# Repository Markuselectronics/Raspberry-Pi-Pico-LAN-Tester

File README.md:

<div align="center">

# Raspberry Pi Pico LAN Tester

### Portable Ethernet diagnostic tool with `W5500`, `OLED`, battery charging and a custom PCB

</div>

---

## Overview

This is a compact handheld LAN tester based on a **Raspberry Pi Pico**, a **W5500 Ethernet controller**, an **SSD1306 OLED display** and **LiPo battery charging**.

It quickly checks whether an Ethernet port is actually working. The tester checks the physical link, requests an IP address with DHCP, shows IP / gateway / DNS information and performs a simple internet connectivity test.

---

## Main Features

- `W5500` Ethernet controller over SPI
- `SSD1306` 128x64 OLED display
- One-button LAN test
- Link, DHCP and internet check
- IP / Gateway / DNS display
- Battery voltage and charging status
- Custom PCB with Raspberry Pi Pico
- 3D printed enclosure

---

## Project Files

The repository contains the firmware and KiCad hardware files:

```text
LANTester/
├── Code/
└── KiCad/
```

`Code` contains the Raspberry Pi Pico firmware.  
`KiCad` contains the schematic, PCB and manufacturing files.

---

## Flashing

If the ready-built `LANTester.uf2` file is included, flashing is simple:

1. Hold **BOOTSEL** on the Raspberry Pi Pico.
2. Plug it into USB.
3. Copy `LANTester.uf2` to the Pico drive.
4. The Pico reboots and starts the firmware.

No special programmer is needed.

---

## Full Build Guide

Instructables:  
https://www.instructables.com/Portable-Raspberry-Pi-Pico-LAN-Tester/

---

## 3D Printed Case

Printables:  
https://www.printables.com/model/1705220-raspberry-pi-pico-lan-tester

---

## Notes

This repository contains the firmware and hardware files for the project.  
Photos, build steps and assembly instructions are documented in the Instructables guide.

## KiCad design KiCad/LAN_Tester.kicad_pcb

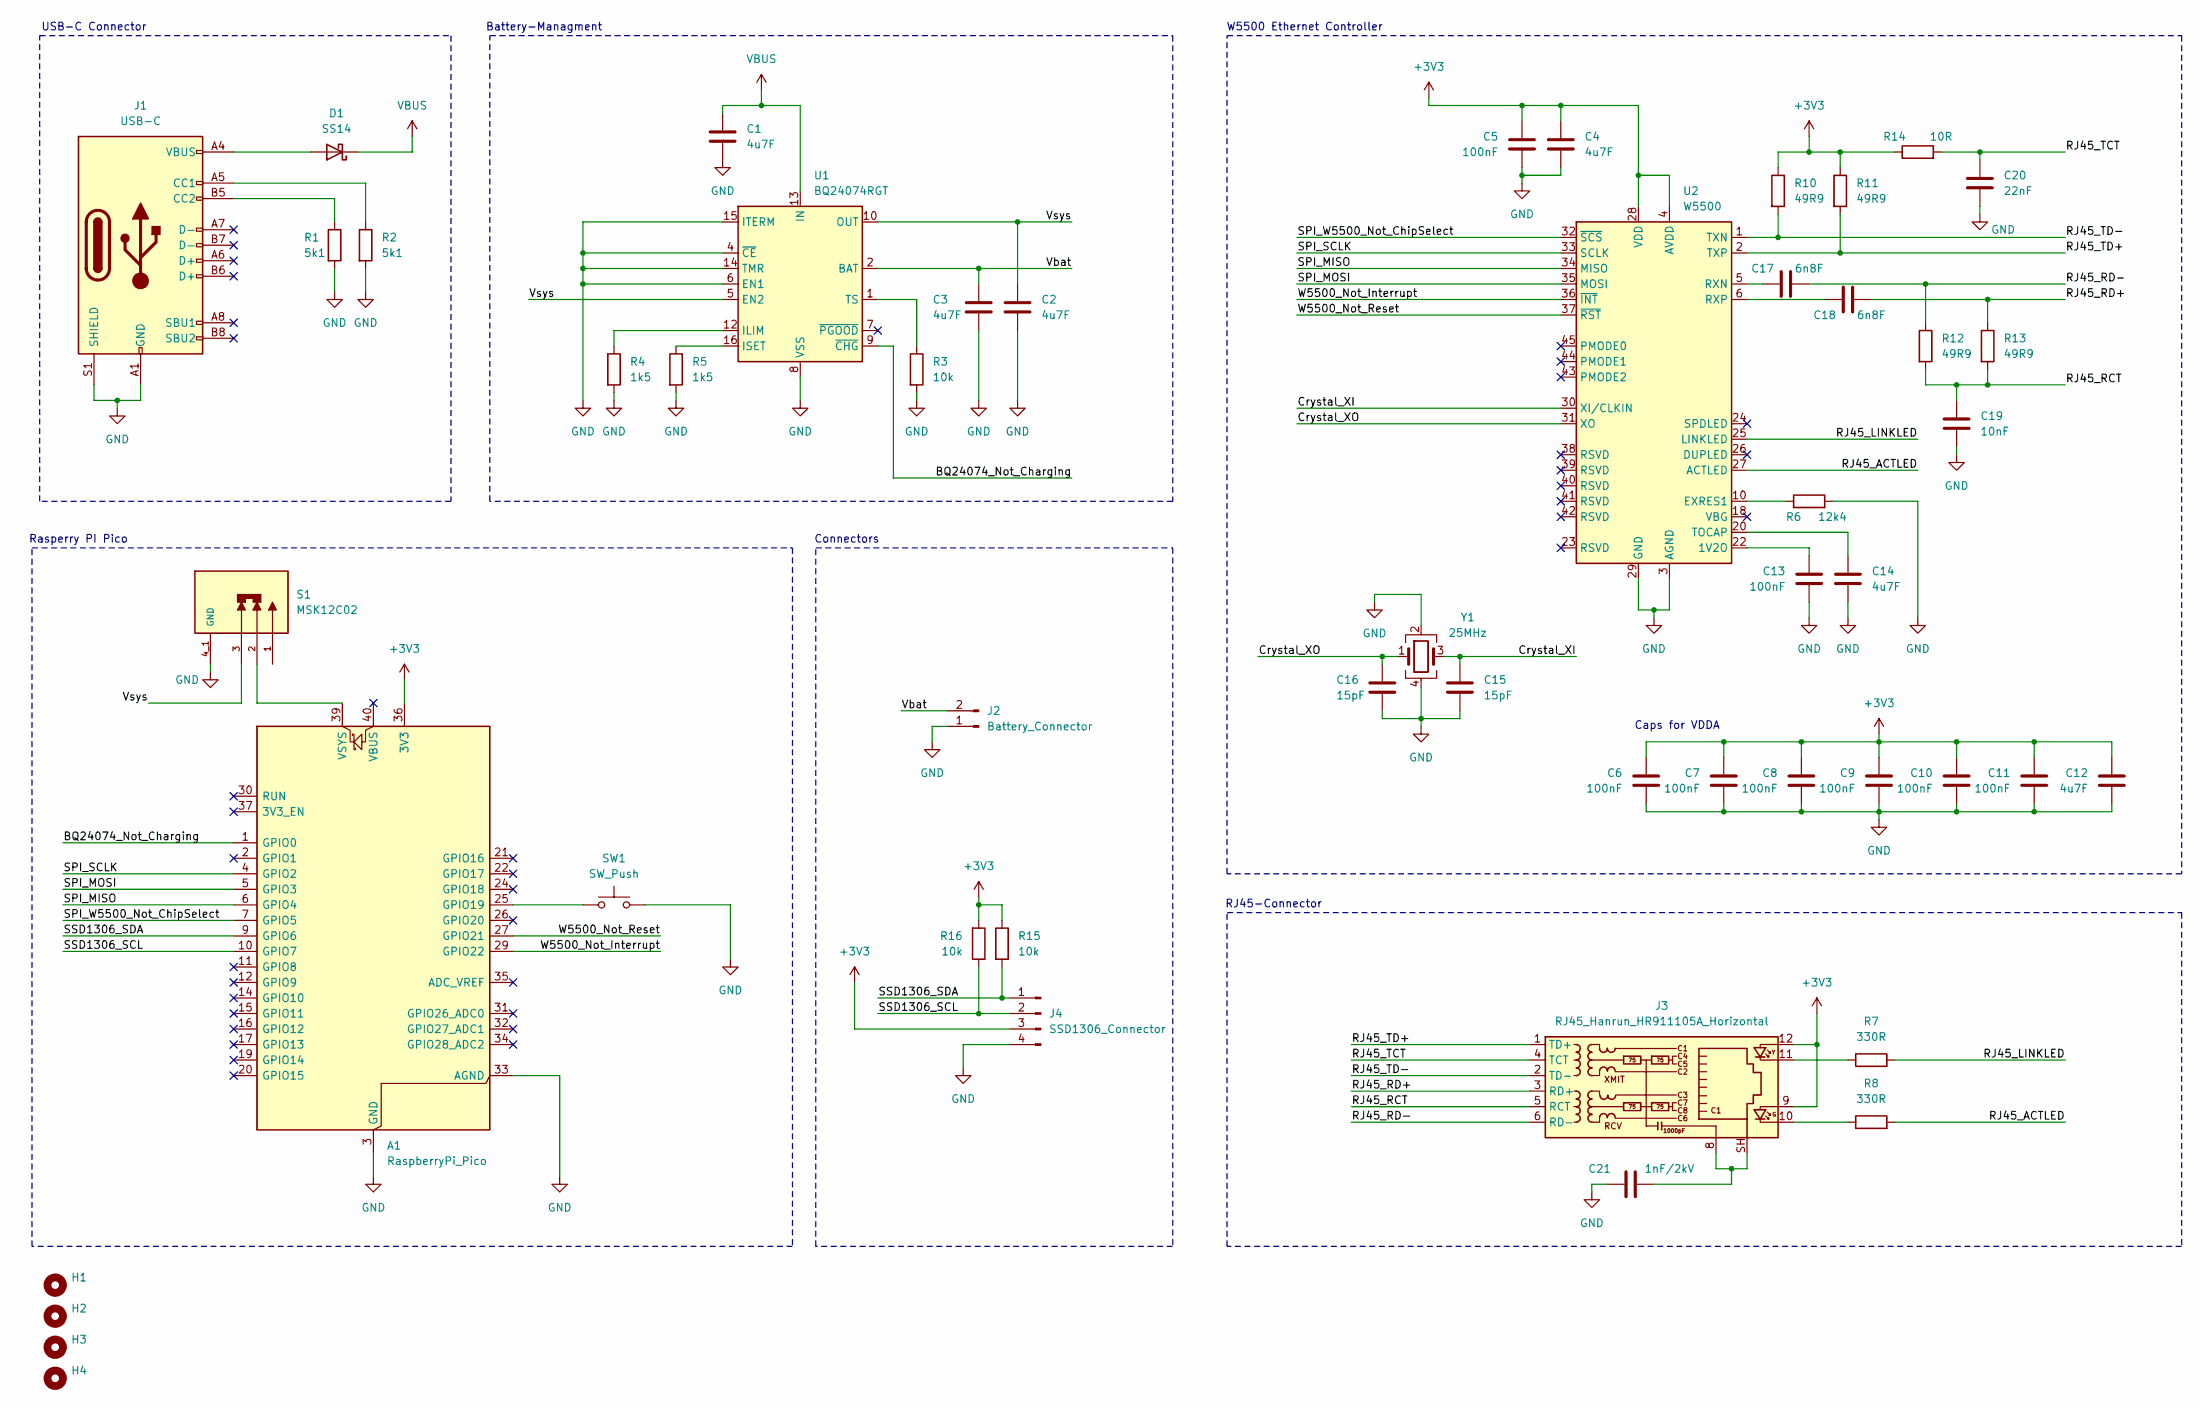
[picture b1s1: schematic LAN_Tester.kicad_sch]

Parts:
A1: RaspberryPi_Pico; RaspberryPi_Pico_SMD
C1, C2, C3, C4, C12, C14: 4u7F; C_0805_2012Metric; LCSC Part # C1779
C5, C6, C7, C8, C9, C10, C11, C13: 100nF; C_0402_1005Metric; LCSC Part # C307331
C15, C16: 15pF; C_0603_1608Metric; LCSC Part # C1644
C17, C18: 6n8F; C_0603_1608Metric; LCSC Part # C1631
C19: 10nF; C_0603_1608Metric; LCSC Part # C57112
C20: 22nF; C_0603_1608Metric; LCSC Part # C1697
C21: 1nF/2kV; C_1206_3216Metric; LCSC Part # C9196
D1: SS14; D_SMA; LCSC Part # C2480
H1, H2, H3, H4: MountingHole; MountingHole_3.5mm
J1: USB-C; SHOU HAN TYPE-C 16PIN 2MD(073); LCSC Part # C2765186
J2: Battery_Connector; JST_PH_S2B-PH-SM4-TB_1x02-1MP_P2.00mm_Horizontal; LCSC Part # C295747
J3: RJ45_Hanrun_HR911105A_Horizontal; LCSC Part # C12074
J4: SSD1306_Connector; PinHeader_1x04_P2.54mm_Vertical
R1, R2: 5k1; C_0603_1608Metric; LCSC Part # C23186
R3, R15, R16: 10k; C_0603_1608Metric; LCSC Part # C25804
R4, R5: 1k5; C_0603_1608Metric; LCSC Part # C22843
R6: 12k4; C_0603_1608Metric; LCSC Part # C22865
R7, R8: 330R; C_0603_1608Metric; LCSC Part # C23138
R10, R11, R12, R13: 49R9; C_0603_1608Metric; LCSC Part # C23184
R14: 10R; C_0603_1608Metric; LCSC Part # C22859
S1: MSK12C02; SW_MSK12C02; PARTREV A/0; LCSC Part # C431540
SW1: SW_Push; SW_PUSH_6mm_H4.3mm; LCSC Part # C29781307
U1: BQ24074RGT; VQFN-16-1EP_3x3mm_P0.5mm_EP1.6x1.6mm; LCSC Part # C2861252
U2: W5500; LQFP-48_7x7mm_P0.5mm; LCSC Part # C32843
Y1: 25MHz; Crystal_SMD_3225-4Pin_3.2x2.5mm; LCSC Part # C9006

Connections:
+3V3: A1.36 (3V3), C4.1, C5.1, C6.1, C7.1, C8.1, C9.1, C10.1, C11.1, C12.1, J3.9, J3.12, J4.3, R10.1, R11.1, R14.1, R15.1, R16.2, U2.4 (AVDD), U2.8 (AVDD), U2.11 (AVDD), U2.15 (AVDD), U2.17 (AVDD), U2.21 (AVDD), U2.28 (VDD)
/BQ24074_Not_Charging: A1.1 (GPIO0), U1.9 (~CHG)
/Crystal_XI: C15.1, U2.30 (XI/CLKIN), Y1.3
/Crystal_XO: C16.1, U2.31 (XO), Y1.1
/RJ45_ACTLED: R8.2, U2.27 (ACTLED)
/RJ45_LINKLED: R7.2, U2.25 (LINKLED)
/RJ45_RCT: C19.1, J3.5 (RCT), R12.2, R13.2
/RJ45_RD+: C18.2, J3.3 (RD+), R13.1
/RJ45_RD-: C17.2, J3.6 (RD-), R12.1
/RJ45_TCT: C20.1, J3.4 (TCT), R14.2
/RJ45_TD+: J3.1 (TD+), R11.2, U2.2 (TXP)
/RJ45_TD-: J3.2 (TD-), R10.2, U2.1 (TXN)
/SPI_MISO: A1.6 (GPIO4), U2.34 (MISO)
/SPI_MOSI: A1.5 (GPIO3), U2.35 (MOSI)
/SPI_SCLK: A1.4 (GPIO2), U2.33 (SCLK)
/SPI_W5500_Not_ChipSelect: A1.7 (GPIO5), U2.32 (~SCS)
/SSD1306_SCL: A1.10 (GPIO7), J4.2, R16.1
/SSD1306_SDA: A1.9 (GPIO6), J4.1, R15.2
/Vbat: C3.1, J2.2, U1.2 (BAT), U1.3 (BAT)
/Vsys: C2.1, S1.3, U1.5 (EN2), U1.10 (OUT), U1.11 (OUT)
/W5500_Not_Interrupt: A1.29 (GPIO22), U2.36 (~INT)
/W5500_Not_Reset: A1.27 (GPIO21), U2.37 (~RST)
GND: A1.3 (GND), A1.8 (GND), A1.13 (GND), A1.18 (GND), A1.23 (GND), A1.28 (GND), A1.33 (AGND), A1.38 (GND), C1.2, C2.2, C3.2, C4.2, C5.2, C6.2, C7.2, C8.2, C9.2, C10.2, C11.2, C12.2, C13.2, C14.2, C15.2, C16.2, C19.2, C20.2, C21.1, J1.A1 (GND), J1.A12 (GND), J1.B1 (GND), J1.B12 (GND), J1.S1 (SHIELD), J2.1, J4.4, R1.2, R2.2, R3.2, R4.2, R5.2, R6.2, S1.4_1 (GND), S1.4_2 (GND), S1.4_3 (GND), S1.4_4 (GND), SW1.2, U1.4 (~CE), U1.6 (EN1), U1.8 (VSS), U1.14 (TMR), U1.15 (ITERM), U1.17 (VSS), U2.3 (AGND), U2.9 (AGND), U2.14 (AGND), U2.16 (AGND), U2.19 (AGND), U2.29 (GND), U2.48 (AGND), Y1.2, Y1.4
unnamed: A1.25 (GPIO19), SW1.1
unnamed: A1.39 (VSYS), S1.2
unnamed: C21.2, J3.8, J3.SH
unnamed: D1.2 (A), J1.A4 (VBUS), J1.A9 (VBUS), J1.B4 (VBUS), J1.B9 (VBUS)
unnamed: J1.A5 (CC1), R2.1
unnamed: J1.B5 (CC2), R1.1
unnamed: J3.10, R8.1
unnamed: J3.11, R7.1
unnamed: R4.1, U1.12 (ILIM)
unnamed: R5.1, U1.16 (ISET)
unnamed: R3.1, U1.1 (TS)
unnamed: C13.1, U2.22 (1V2O)
unnamed: R6.1, U2.10 (EXRES1)
unnamed: C17.1, U2.5 (RXN)
unnamed: C18.1, U2.6 (RXP)
unnamed: C14.1, U2.20 (TOCAP)
VBUS: C1.1, D1.1 (K), U1.13 (IN)

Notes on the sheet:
Rasperry PI Pico
Caps for VDDA
RJ45-Connector
Connectors
Battery-Managment
W5500 Ethernet Controller
USB-C Connector

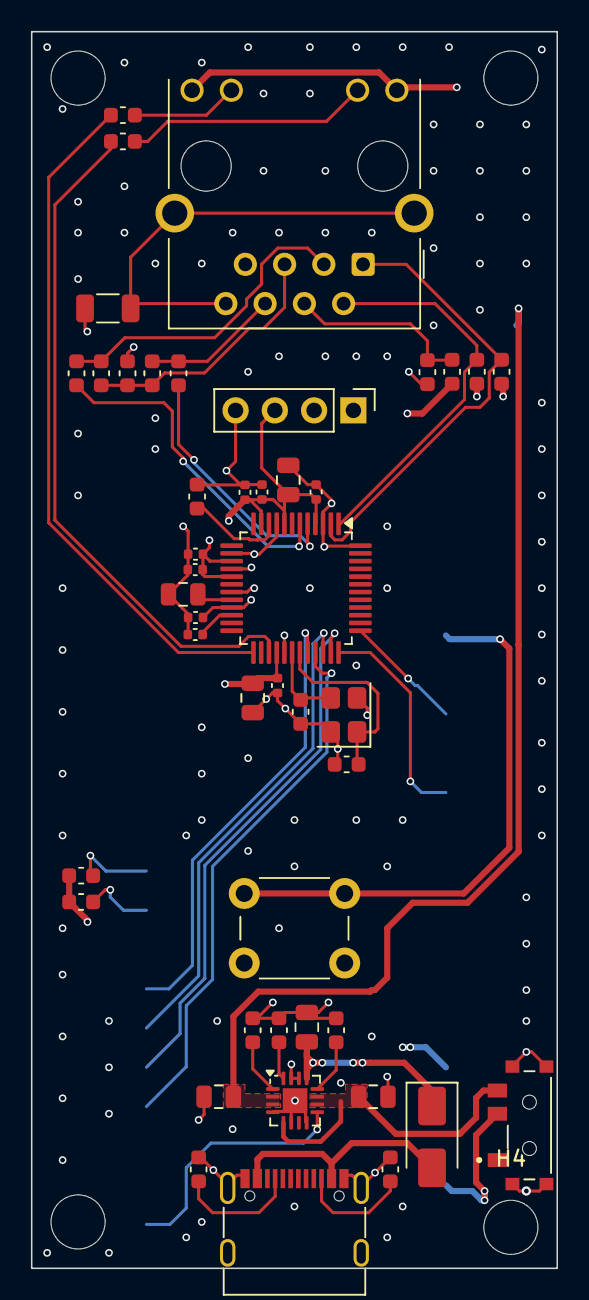
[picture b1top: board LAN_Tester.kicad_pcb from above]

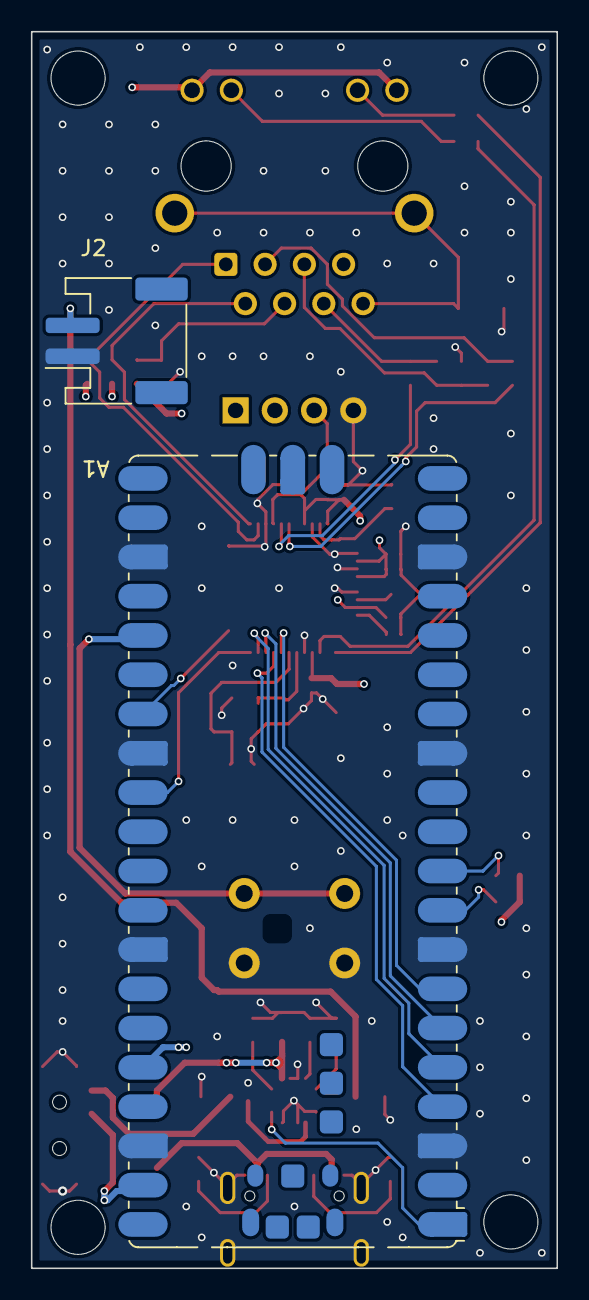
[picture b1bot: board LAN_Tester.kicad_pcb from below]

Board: 4 copper layers, 34.0 x 80.0 mm, 51 parts (2 on the bottom side), 40 nets.

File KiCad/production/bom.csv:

Designator,Footprint,Quantity,Value,LCSC Part #
A1,RaspberryPi_Pico_SMD,1,RaspberryPi_Pico,
"C1, C12, C14, C2, C3, C4",0805,6,4u7F,C1779
"C10, C11, C13, C5, C6, C7, C8, C9",0402,8,100nF,C307331
"C15, C16",0603,2,15pF,C1644
"C17, C18",0603,2,6n8F,C1631
C19,0603,1,10nF,C57112
C20,0603,1,22nF,C1697
C21,1206,1,1nF/2kV,C9196
D1,D_SMA,1,SS14,C2480
J1,SHOU HAN TYPE-C 16PIN 2MD(073),1,USB-C,C2765186
J2,JST_PH_S2B-PH-SM4-TB_1x02-1MP_P2.00mm_Horizontal,1,Battery_Connector,C295747
J3,RJ45_Hanrun_HR911105A_Horizontal,1,RJ45_Hanrun_HR911105A_Horizontal,C12074
"R1, R2",0603,2,5k1,C23186
"R10, R11, R12, R13",0603,4,49R9,C23184
R14,0603,1,10R,C22859
"R15, R16, R3",0603,3,10k,C25804
"R4, R5",0603,2,1k5,C22843
R6,0603,1,12k4,C22865
"R7, R8",0603,2,330R,C23138
R9,0603,1,1M,C22935
S1,SW_MSK12C02,1,MSK12C02,C431540
U1,VQFN-16-1EP_3x3mm_P0.5mm_EP1.6x1.6mm,1,BQ24074RGT,C2861252
U2,LQFP-48_7x7mm_P0.5mm,1,W5500,C32843
Y1,Crystal_SMD_3225-4Pin_3.2x2.5mm,1,25MHz,C9006

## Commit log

2026-04-29 Initial project upload
2026-04-29 Add firmware UF2 and update files
2026-04-29 Improve README and add overview image
2026-04-29 Fix README formatting and add Instructables link
2026-04-29 Add Printables link
2026-04-29 Simplify README links
